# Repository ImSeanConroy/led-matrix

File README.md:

# LED Matrix

This project is a minimal, compact 12-pixel LED matrix (2 rows × 6 columns), based on WS2812D addressable LEDs and created using KiCad.

## Getting Started

1. **Open the Project** - Open the `.kicad_pro` file in KiCad to view the project.
2. **Review the Design** - Inspect the schematic and PCB layout to ensure it meets your needs.
3. **Customize or Export** - Make any modifications and export the Gerber files for fabrication.
4. **Order the PCB** - Submit the Gerber files to your preferred PCB manufacturer.
5. **Get the Components** - Purchase the components from the BOM and a compatible board.
6. **Assemble the Hardware** - Solder the components and assemble the board.
7. **Upload the Firmware** - Connect the board via USB and upload the firmware.

## Required Components

The following are the required components to build the 2x6 LED Matrix:

| Quantity | Component | Description | Source |
| - | - | - | - |
| 12 | WS2812D 8mm LEDs | Individually addressable RGB LEDs | [AliExpress](https://aliexpress.bitluni.net/ws2812d) |
| 1 | 2×03 Pin Header | 2-row, 3-pin male header | [AliExpress](https://aliexpress.bitluni.net/ws2812d) |

## Contributing

Contributions are welcome. Please open an issue or submit a pull request for any enhancements or bug fixes.

## License

This project is Distributed under the MIT License - see the [LICENSE](LICENSE) file for information.

## Support

If you are having problems, please let me know by [raising a new issue](https://github.com/ImSeanConroy/led-matrix/issues/new/choose).

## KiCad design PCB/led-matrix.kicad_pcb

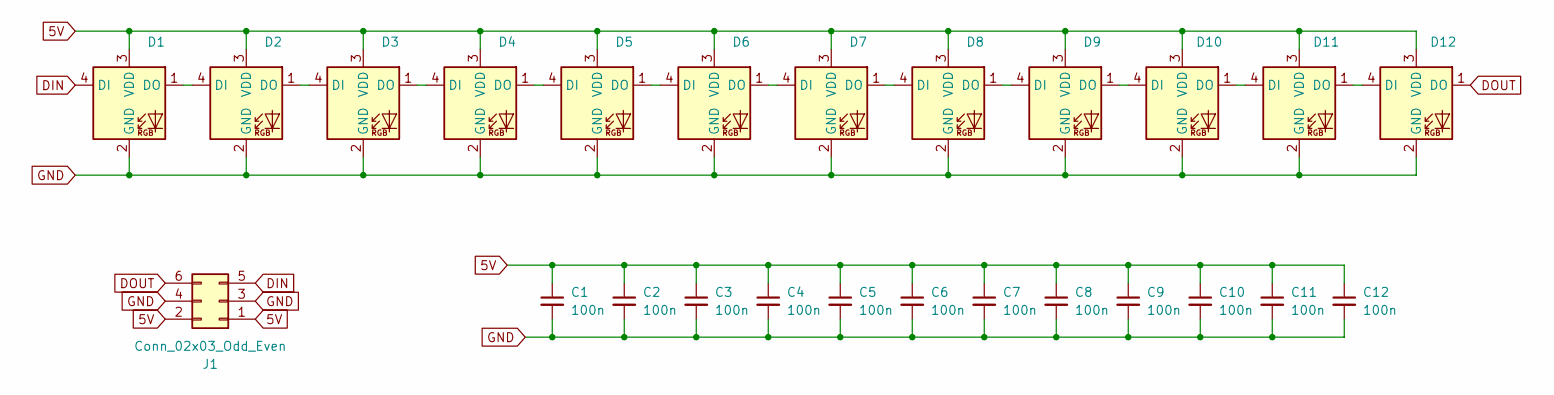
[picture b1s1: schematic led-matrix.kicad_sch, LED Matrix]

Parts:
C1, C2, C3, C4, C5, C6, C7, C8, C9, C10, C11, C12: 100n; C_0603_1608Metric
D1, D2, D3, D4, D5, D6, D7, D8, D9, D10, D11, D12: APA-106-F5; WS2812D
J1: Conn_02x03_Odd_Even; PinHeader_2x03_P2.54mm_Vertical_SMD

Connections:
5V: C1.1, C2.1, C3.1, C4.1, C5.1, C6.1, C7.1, C8.1, C9.1, C10.1, C11.1, C12.1, D1.3 (VDD), D2.3 (VDD), D3.3 (VDD), D4.3 (VDD), D5.3 (VDD), D6.3 (VDD), D7.3 (VDD), D8.3 (VDD), D9.3 (VDD), D10.3 (VDD), D11.3 (VDD), D12.3 (VDD), J1.1, J1.2
DIN: D1.4 (DI), J1.5
DOUT: D12.1 (DO), J1.6
GND: C1.2, C2.2, C3.2, C4.2, C5.2, C6.2, C7.2, C8.2, C9.2, C10.2, C11.2, C12.2, D1.2 (GND), D2.2 (GND), D3.2 (GND), D4.2 (GND), D5.2 (GND), D6.2 (GND), D7.2 (GND), D8.2 (GND), D9.2 (GND), D10.2 (GND), D11.2 (GND), D12.2 (GND), J1.3, J1.4
unnamed: D1.1 (DO), D2.4 (DI)
unnamed: D2.1 (DO), D3.4 (DI)
unnamed: D3.1 (DO), D4.4 (DI)
unnamed: D4.1 (DO), D5.4 (DI)
unnamed: D5.1 (DO), D6.4 (DI)
unnamed: D6.1 (DO), D7.4 (DI)
unnamed: D7.1 (DO), D8.4 (DI)
unnamed: D8.1 (DO), D9.4 (DI)
unnamed: D9.1 (DO), D10.4 (DI)
unnamed: D10.1 (DO), D11.4 (DI)
unnamed: D11.1 (DO), D12.4 (DI)

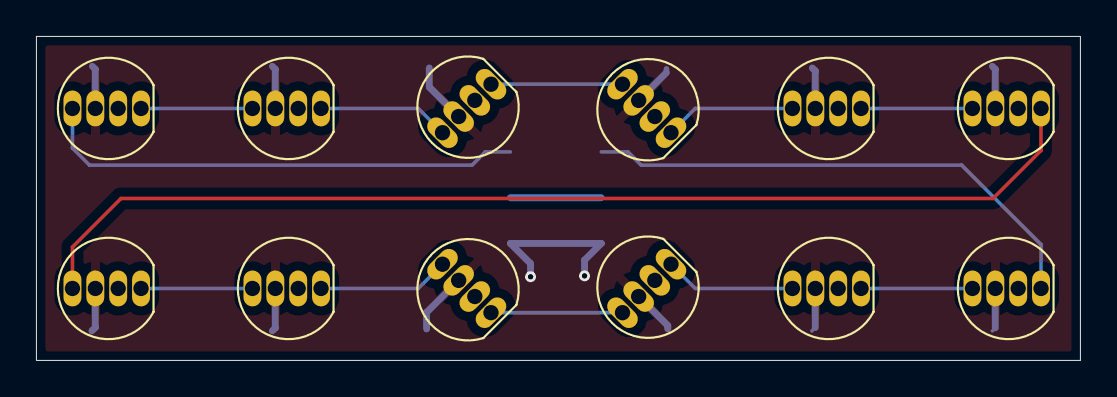
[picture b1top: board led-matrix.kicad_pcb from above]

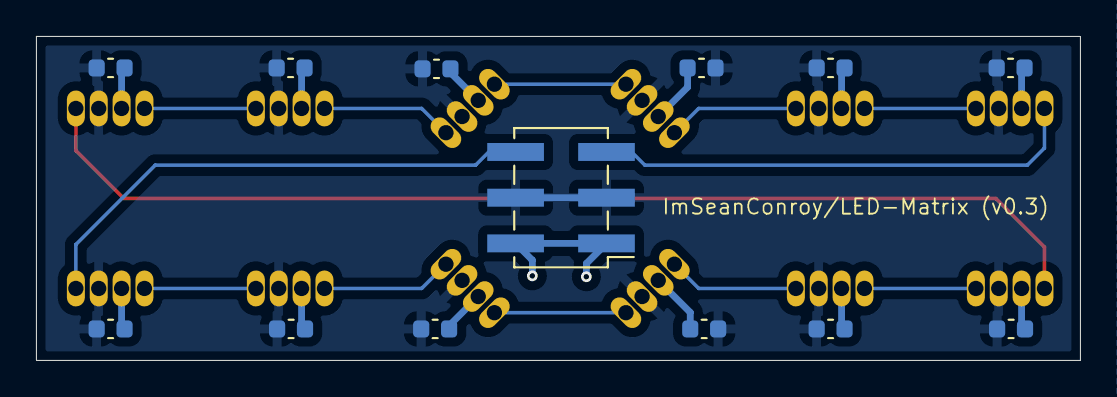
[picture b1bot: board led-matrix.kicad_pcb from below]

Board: 2 copper layers, 58.0 x 18.0 mm, 25 parts (13 on the bottom side), 15 nets.

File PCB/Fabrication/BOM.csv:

"Id";"Designator";"Footprint";"Quantity";"Designation";"Supplier and ref";
1;"D2,D9,D5,D11,D10,D1,D6,D12,D7,D8,D3,D4";"WS2812D";12;"APA-106-F5";;;
2;"C12,C7,C6,C8,C4,C1,C2,C5,C9,C10,C3,C11";"C_0603_1608Metric";12;"100n";;;
3;"J1";"PinHeader_2x03_P2.54mm_Vertical_SMD";1;"Conn_02x03_Odd_Even";;;

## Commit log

2025-06-14 Add kicad libraries
2025-06-14 Layout schematic
2025-06-14 Layout board
2025-06-14 Rearrange board layout
2025-06-22 Add bill of materials
2025-06-25 Add led test script and increase pad size
2025-07-13 Resolve ground plane island issue
2025-07-13 Add breath, chaser, rainbow and status firmware
2025-07-14 Add repo image
